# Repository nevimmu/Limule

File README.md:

# Limule Keyboard

A split ergonomic keyboard powered by ZMK firmware.

## Features

*   **Split Layout:** Two separate halves for ergonomic hand positioning.
*   **30 Keys per Half:** A compact and efficient layout.
*   **nice!nano Controller:** Powered by the nice!nano, a Pro Micro-compatible controller with BLE and LiPo charging.
*   **nice!view Screen:** Low power information screen
*   **ZMK Firmware:** Runs on the powerful and flexible ZMK firmware.
*   **Ergogen Design:** The PCB was designed using [Ergogen](https://ergogen.xyz/).

## Thanks
TODO: add the projects that helped me

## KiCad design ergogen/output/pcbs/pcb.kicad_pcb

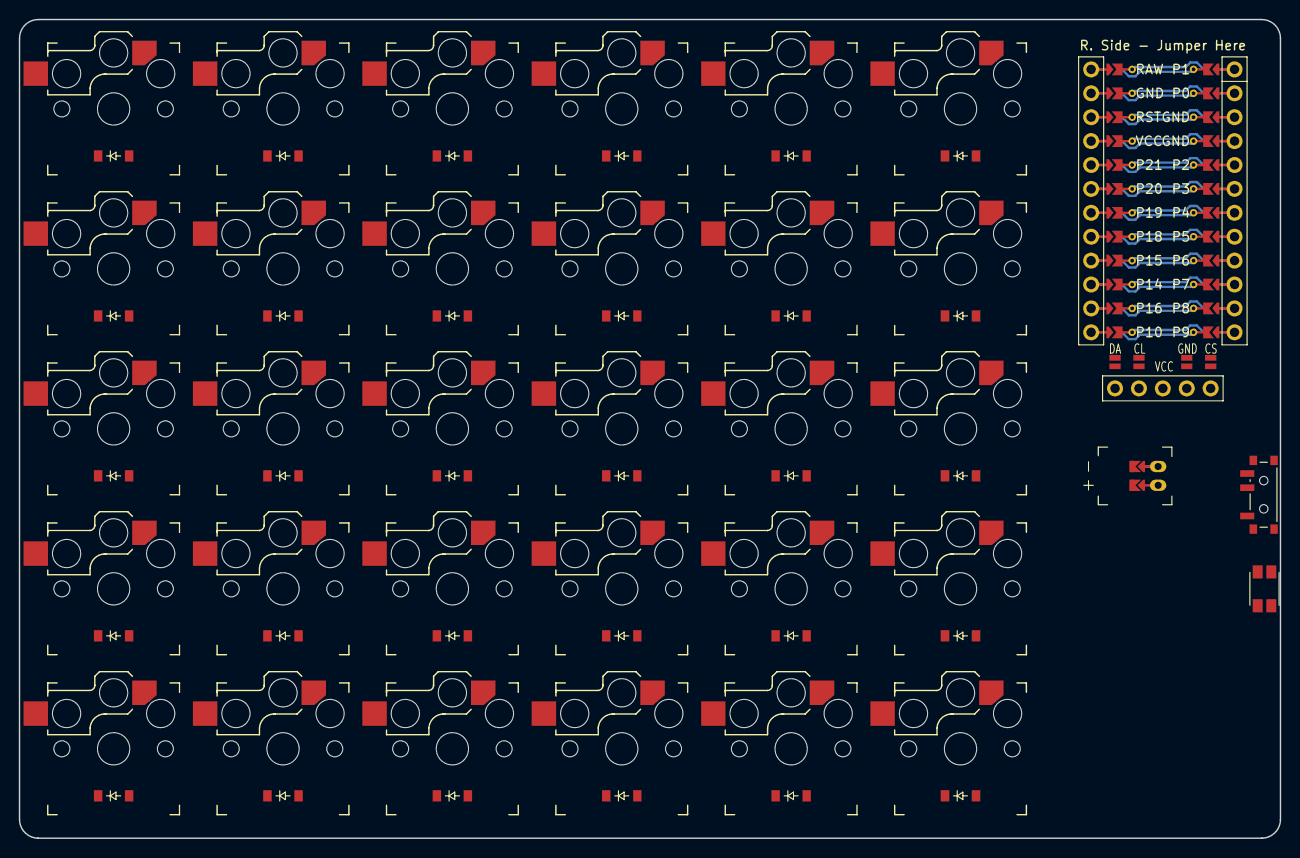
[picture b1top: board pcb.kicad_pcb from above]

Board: 2 copper layers, 134.0 x 87.0 mm, 65 parts (0 on the bottom side), 44 nets.

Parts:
D1, D2, D3, D4, D5, D6, D7, D8, D9, D10, D11, D12, D13, D14, D15, D16, D17, D18, D19, D20, D21, D22, D23, D24, D25, D26, D27, D28, D29, D30: ComboDiode
DISP1: nice!view
JST1: battery_connector_jst_ph_2
MCU1: nice_nano
S1, S2, S3, S4, S5, S6, S7, S8, S9, S10, S11, S12, S13, S14, S15, S16, S17, S18, S19, S20, S21, S22, S23, S24, S25, S26, S27, S28, S29, S30: PG1350
SW1: sw_reset_side
SW2: power_switch

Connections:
BAT_P: JST1.1, SW2.2, SW2.5
CS: DISP1.17, DISP1.27
DISP1_1: DISP1.1, DISP1.10, DISP1.23
DISP1_2: DISP1.2, DISP1.11, DISP1.22
DISP1_4: DISP1.4, DISP1.12, DISP1.21
DISP1_5: DISP1.5, DISP1.13, DISP1.20
GND: DISP1.16, DISP1.26, JST1.2, MCU1.2, MCU1.121, MCU1.122, SW1.1
JST1_1: JST1.11, JST1.21, JST1.31
JST1_2: JST1.12, JST1.22, JST1.32
MOSI: DISP1.14, DISP1.24
RAW: MCU1.1, SW2.3, SW2.6
RST: MCU1.3, SW1.2
SCK: DISP1.15, DISP1.25
VCC: DISP1.3, MCU1.4
index_bottom: D22.2, S22.2
index_home: D23.2, S23.2
index_mod: D21.2, S21.2
index_number: D25.2, S25.2
index_top: D24.2, S24.2
inner_bottom: D27.2, S27.2
inner_home: D28.2, S28.2
inner_mod: D26.2, S26.2
inner_number: D30.2, S30.2
inner_top: D29.2, S29.2
middle_bottom: D17.2, S17.2
middle_home: D18.2, S18.2
middle_mod: D16.2, S16.2
middle_number: D20.2, S20.2
middle_top: D19.2, S19.2
outer_bottom: D2.2, S2.2
outer_home: D3.2, S3.2
outer_mod: D1.2, S1.2
outer_number: D5.2, S5.2
outer_top: D4.2, S4.2
pinky_bottom: D7.2, S7.2
pinky_home: D8.2, S8.2
pinky_mod: D6.2, S6.2
pinky_number: D10.2, S10.2
pinky_top: D9.2, S9.2
ring_bottom: D12.2, S12.2
ring_home: D13.2, S13.2
ring_mod: D11.2, S11.2
ring_number: D15.2, S15.2
ring_top: D14.2, S14.2

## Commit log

2025-04-26 Added infused-kim footprint submodule for ergogen
2025-04-26 Changed the footprints.
2025-04-27 Added ceoloide footprints submodule for ergogen.
2025-04-27 Added components.
2025-08-10 feat(build): removed the raw output from the repo
    board will be added to the repo in another folder with the traces done in a final state
2025-08-10 Added package.json
2025-08-10 docs: added README
2025-08-18 feat(ergogen): added footprint to add text to the board
2025-08-18 feat(ergogen): added backtext to mirror the front text
2025-08-28 feat(ergogen): added connections, added text, silk art, holes for the cover
2025-08-29 feat(ergogen): added top plate
2025-08-30 Changed the name of the keyboard
2025-09-06 feat(ergogen): added routes for keys
2025-09-08 style(ergogen): format
2025-09-08 feat(ergogen): added routes from the row and cols to the nano
2025-09-28 feat(ergogen): changed the artwork position
2025-11-10 feat(ergogen): add initial flake.nix and flake.lock files for project setup
